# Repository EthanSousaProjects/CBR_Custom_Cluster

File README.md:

# CBR_Custom_Cluster

A custom cluster design for my CBR 125RW6 (2006 carburetor model) to replace the old large mechanical cluster with a smaller simpler design.

The `references` folder contains details on set things on the bike (eg. hole position dimensions, resistance of stock sensor) and thus design requirements, calculations and decisions can be found here.

## License

There are three licenses for this project. All code falls under the AGPLV3 license, all hardware designs fall under the CERN-OHL-S license, all artwork and documentation in the READMEs related to this project are under the CC By-SA license.

This project is based around creating a dash for a honda motorcycle. I have no affiliation with honda or its subsidiaries. This is not an official honda project in anyway.

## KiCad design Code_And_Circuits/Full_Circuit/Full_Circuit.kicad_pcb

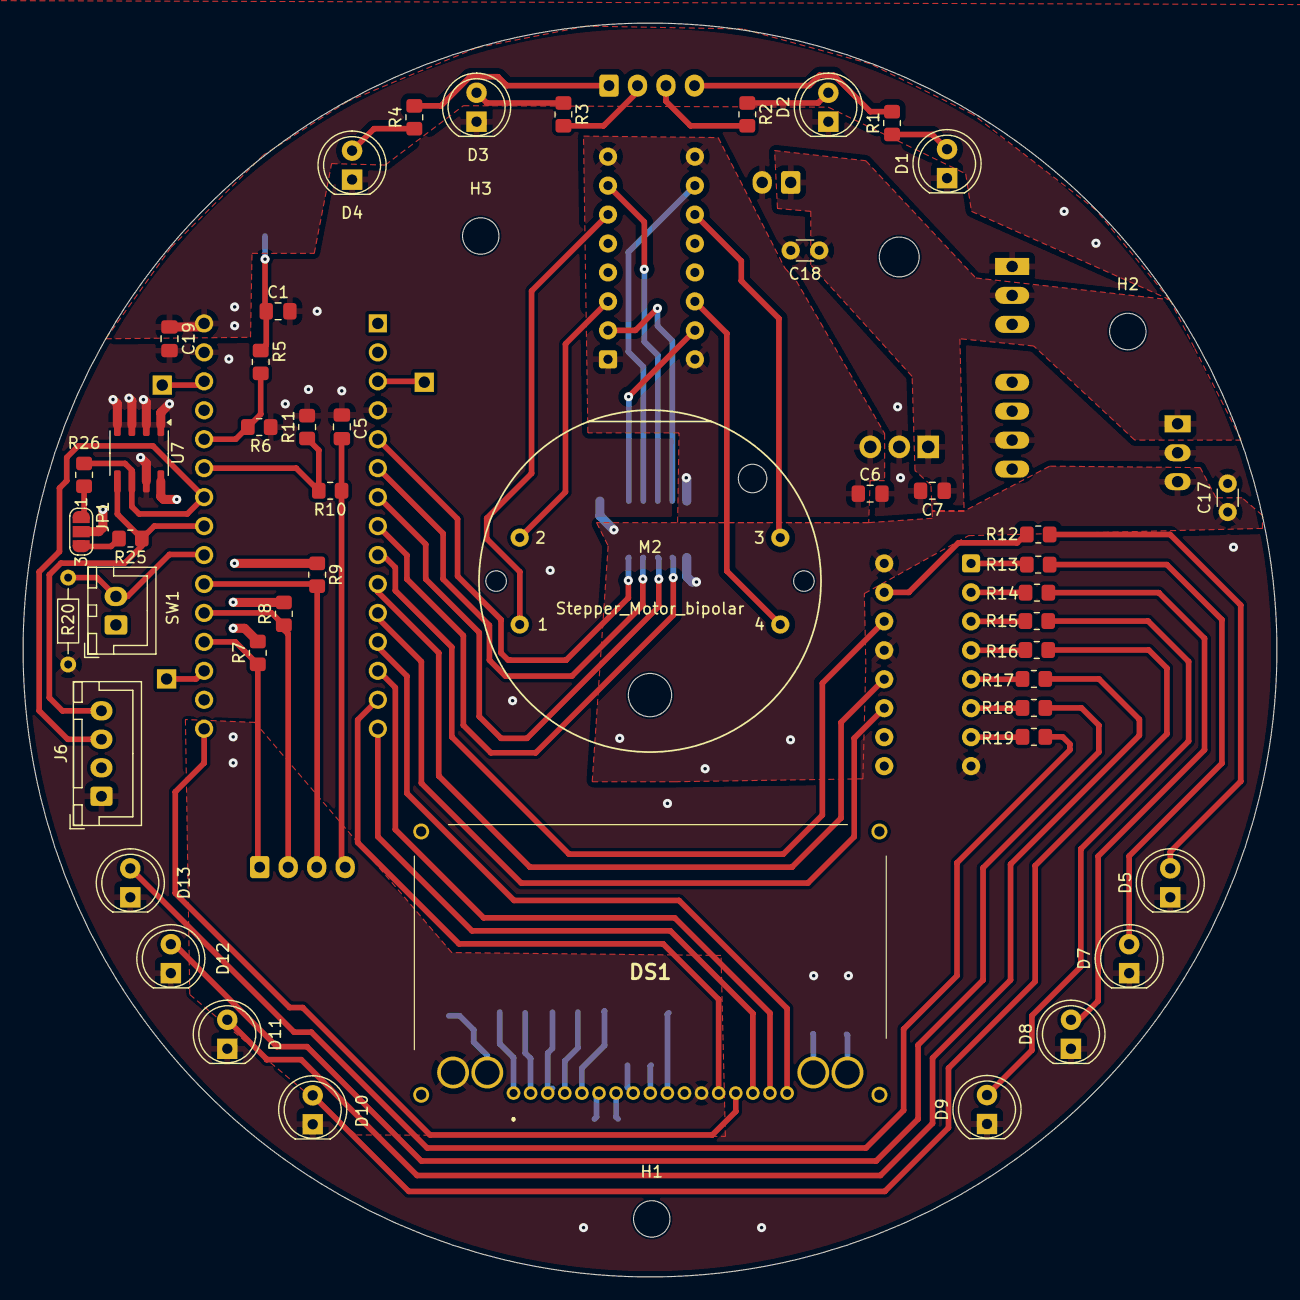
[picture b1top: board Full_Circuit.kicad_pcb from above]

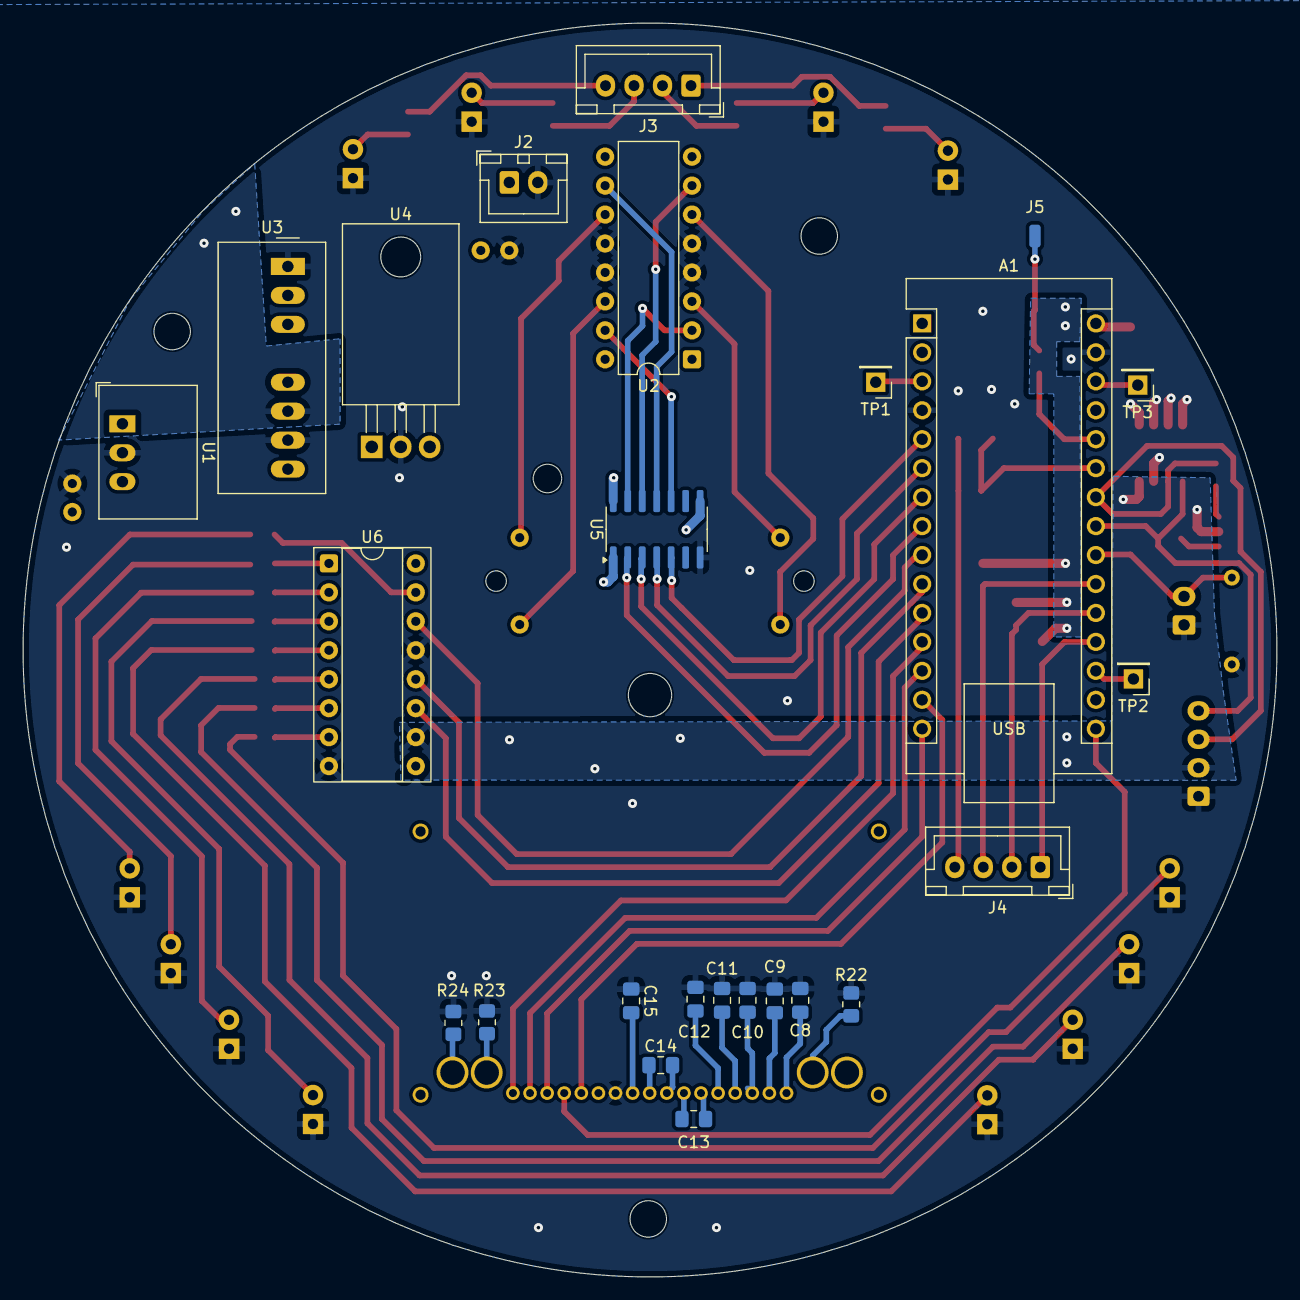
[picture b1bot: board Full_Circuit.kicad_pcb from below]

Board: 2 copper layers, 110.0 x 110.0 mm, 76 parts (25 on the bottom side), 77 nets.

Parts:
A1: Arduino_Nano_ESP32; Arduino_Nano
C1, C5: 1000PF; C_0805_2012Metric_Pad1.18x1.45mm_HandSolder
C6, C19: 0.1 uF; C_0805_2012Metric_Pad1.18x1.45mm_HandSolder
C7: 0.33uF; C_0805_2012Metric_Pad1.18x1.45mm_HandSolder
C8, C9, C10, C11, C12, C13, C14, C15: 1uF; C_0805_2012Metric_Pad1.18x1.45mm_HandSolder
C17, C18: 10 uF; C_Disc_D3.0mm_W1.6mm_P2.50mm
D1: LED_Right_Indicator(Yellow_LTH5MM12VFR4700); LED_D5.0mm
D2: LED_High_Beam(Blue_LTH5MM12VFR4600); LED_D5.0mm
D3: LED_Neutral(Green_LTH5MM12VFR4500); LED_D5.0mm
D4: LED_Left_Indicator(Yellow_LTH5MM12VFR4700); LED_D5.0mm
D5, D7, D8, D9, D10, D11, D12, D13: LED_2.2V_20ma; LED_D5.0mm
DS1: NHD-C12832A1Z-FS_RGB_-FBW-3V; NHDC12832A1ZFSRGBFBW3V
H1, H2, H3: MountingHole; MountingHole_3.2mm_M3
J2: Main_Power_In_JST-XH; JST_XH_B2B-XH-A_1x02_P2.50mm_Vertical
J3: Warning_Lights_JST-XH; JST_XH_B4B-XH-A_1x04_P2.50mm_Vertical
J4: Signals_RPM_Temp_Fuel_JST-XH; JST_XH_B4B-XH-A_1x04_P2.50mm_Vertical
J5: Speed_Pulser_Setup_Signal_JST-XH; SolderWirePad_1x01_SMD_1x2mm
J6: Alphanumeric_Qwiick_JST-XH; JST_XH_B4B-XH-A_1x04_P2.50mm_Vertical
JP1: Pull up Jumper; SolderJumper-3_P1.3mm_Open_RoundedPad1.0x1.5mm_NumberLabels
M2: Stepper_Motor_bipolar; X27-168
N1: Tachometer Reference; Dial_Gauge_Reference_CBF600
R1, R2, R3, R4: 200R; R_0805_2012Metric_Pad1.20x1.40mm_HandSolder
R5, R10: 3.3KR; R_0805_2012Metric_Pad1.20x1.40mm_HandSolder
R6, R7, R8, R11: 1KR; R_0805_2012Metric_Pad1.20x1.40mm_HandSolder
R9: 510R; R_0805_2012Metric_Pad1.20x1.40mm_HandSolder
R12, R13, R14, R15, R16, R17, R18, R19: 100R; R_0805_2012Metric_Pad1.20x1.40mm_HandSolder
R20: 10KR; R_Axial_DIN0204_L3.6mm_D1.6mm_P7.62mm_Horizontal
R22: 56R; R_0805_2012Metric_Pad1.20x1.40mm_HandSolder
R23, R24: 6.8R; R_0805_2012Metric_Pad1.20x1.40mm_HandSolder
R25, R26: 4.7KR; R_0805_2012Metric_Pad1.20x1.40mm_HandSolder
SW1: SW_Push_JST-XH_Input; JST_XH_B2B-XH-A_1x02_P2.50mm_Vertical
TP1, TP2, TP3: TestPoint; PinHeader_1x01_P2.54mm_Vertical
U1: R-78E3.3-0.5; Converter_DCDC_RECOM_R-78E-0.5_THT
U2: L293D; DIP-16_W7.62mm
U3: TEC2-1219WI; Converter_DCDC_TRACO_TMR-xxxx_THT
U4: L7805; TO-220-3_Horizontal_TabDown
U5: TXB0104D; SOIC-14_3.9x8.7mm_P1.27mm
U6: 74HC595; DIP-16_W7.62mm_Socket
U7: CAT24C128; SOIC-8_3.9x4.9mm_P1.27mm

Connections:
+3.3V: C17.1, DS1.12 (VDD), DS1.A1 (COMMON_ANODE), J6.2, JP1.2 (C), SW1.1, U1.3 (OUT), U5.1 (VCCA), U5.8 (OE), U6.10 (~SRCLR), U6.16 (VCC), U7.8 (VCC)
+5V: C6.1, U2.1 (EN1,2), U2.8 (VCC2), U2.9 (EN3,4), U2.16 (VCC1), U4.3 (OUT), U5.14 (VCCB)
+9V: A1.30 (VIN), C19.1, R7.2, R8.2, R9.1, U3.6 (+Vout)
+12V: C7.1, C18.1, J2.1, U1.1 (IN), U3.2 (+Vin), U4.1 (IN)
/Data_Display_Controller/A0: A1.15 (D12/CIPO), DS1.15 (A0)
/Data_Display_Controller/Bar_RCLK: A1.10 (D7), U6.12 (RCLK)
/Data_Display_Controller/Bar_SER: A1.9 (D6), U6.14 (SER)
/Data_Display_Controller/Bar_SRCLK: A1.11 (D8), U6.11 (SRCLK)
/Data_Display_Controller/Button_A: A1.22 (A3), R20.2, SW1.2
/Data_Display_Controller/COPI(MOSI): A1.14 (D11/COPI), DS1.13 (SI)
/Data_Display_Controller/Coolant: A1.21 (A2), J4.3, R9.2
/Data_Display_Controller/Fuel_A: A1.19 (A0), J4.1, R7.1
/Data_Display_Controller/Fuel_B: A1.20 (A1), J4.2, R8.1
/Data_Display_Controller/I2C SCL: A1.24 (SCL/A5), J6.3, R26.1, U7.6 (SCL)
/Data_Display_Controller/I2C SDA: A1.23 (SDA/A4), J6.4, R25.1, U7.5 (SDA)
/Data_Display_Controller/RES(RST): A1.13 (D10/CS), DS1.16 (~RES)
/Data_Display_Controller/RPM_Pulse: A1.25 (A6), R10.2, R11.1
/Data_Display_Controller/SPI_CS(CS1B): A1.12 (D9), DS1.17 (CS1B)
/Data_Display_Controller/SPI_SCK: A1.16 (D13/SCK), DS1.14 (SCL)
/Data_Display_Controller/Speed_Pulse: A1.26 (A7), R5.2, R6.1
/Data_Display_Controller/Tach_A1: A1.8 (D5), U5.2 (A1)
/Data_Display_Controller/Tach_A2: A1.7 (D4), U5.3 (A2)
/Data_Display_Controller/Tach_A3: A1.6 (D3), U5.4 (A3)
/Data_Display_Controller/Tach_A4: A1.5 (D2), U5.5 (A4)
GND: A1.4 (GND), A1.29 (GND), C1.2, C5.1, C6.2, C7.2, C8.1, C9.1, C10.1, C11.1, C12.1, C15.1, C17.2, C18.2, C19.2, D1.1 (K), D2.1 (K), D3.1 (K), D4.1 (K), D5.1 (K), D7.1 (K), D8.1 (K), D9.1 (K), D10.1 (K), D11.1 (K), D12.1 (K), D13.1 (K), DS1.11 (VSS), J2.2, J6.1, R6.2, R11.2, R20.1, R22.2, R23.2, R24.2, U1.2 (GND), U2.4 (GND), U2.5 (GND), U2.12 (GND), U2.13 (GND), U3.1 (-Vin), U3.7 (-Vout), U4.2 (GND), U5.7 (GND), U6.8 (GND), U6.13 (~OE), U7.1 (A0), U7.2 (A1), U7.3 (A2), U7.4 (GND), U7.7 (WP)
unnamed: A1.18 (B0), TP2.1
unnamed: A1.28 (B1), TP3.1
unnamed: A1.3 (~RESET), TP1.1
unnamed: D1.2 (A), R1.1
unnamed: D2.2 (A), R2.1
unnamed: D3.2 (A), R3.1
unnamed: D4.2 (A), R4.1
unnamed: D5.2 (A), R12.1
unnamed: D7.2 (A), R13.1
unnamed: D8.2 (A), R14.1
unnamed: D9.2 (A), R15.1
unnamed: D10.2 (A), R16.1
unnamed: D11.2 (A), R17.1
unnamed: D12.2 (A), R18.1
unnamed: D13.2 (A), R19.1
unnamed: C14.2, DS1.8 (C1+)
unnamed: C14.1, DS1.9 (C1-)
unnamed: C13.1, DS1.7 (C2+)
unnamed: C13.2, DS1.6 (C2-)
unnamed: DS1.K2 (CATHODE_1), R23.1
unnamed: DS1.K3 (CATHODE_2), R24.1
unnamed: DS1.K1 (CATHODE_), R22.1
unnamed: C8.2, DS1.1 (V0)
unnamed: C9.2, DS1.2 (V1)
unnamed: C10.2, DS1.3 (V2)
unnamed: C11.2, DS1.4 (V3)
unnamed: C12.2, DS1.5 (V4)
unnamed: C15.2, DS1.10 (VOUT)
unnamed: J3.1, R4.2
unnamed: J3.2, R3.2
unnamed: J3.3, R2.2
unnamed: J3.4, R1.2
unnamed: C5.2, J4.4, R10.1
unnamed: C1.1, J5.1, R5.1
unnamed: JP1.1 (A), R26.2
unnamed: JP1.3 (B), R25.2
unnamed: M2.2 (-), U2.3 (1Y)
unnamed: U2.2 (1A), U5.13 (B1)
unnamed: U2.7 (2A), U5.12 (B2)
unnamed: M2.1, U2.6 (2Y)
unnamed: U2.10 (3A), U5.11 (B3)
unnamed: M2.3, U2.11 (3Y)
unnamed: U2.15 (4A), U5.10 (B4)
unnamed: M2.4, U2.14 (4Y)
unnamed: R12.2, U6.15 (QA)
unnamed: R13.2, U6.1 (QB)
unnamed: R14.2, U6.2 (QC)
unnamed: R15.2, U6.3 (QD)
unnamed: R16.2, U6.4 (QE)
unnamed: R17.2, U6.5 (QF)
unnamed: R18.2, U6.6 (QG)
unnamed: R19.2, U6.7 (QH)

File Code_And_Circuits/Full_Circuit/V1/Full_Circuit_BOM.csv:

"Reference","Qty","Value","DNP","Exclude from BOM","Exclude from Board","Footprint","Datasheet"
"A1","1","Arduino_Nano_ESP32","","","","Module:Arduino_Nano","https://docs.arduino.cc/resources/datasheets/ABX00083-datasheet.pdf"
"A3","1","Arduino_Nano_ESP32","DNP","","Excluded from board","Module:Arduino_Nano","https://docs.arduino.cc/resources/datasheets/ABX00083-datasheet.pdf"
"C1,C5","2","1000PF","","","","Capacitor_SMD:C_0805_2012Metric_Pad1.18x1.45mm_HandSolder","~"
"C2,C3,C4","3","1000PF","DNP","","Excluded from board","Capacitor_THT:C_Disc_D3.0mm_W2.0mm_P2.50mm","~"
"C6,C19","2","0.1 uF","","","","Capacitor_SMD:C_0805_2012Metric_Pad1.18x1.45mm_HandSolder","~"
"C7","1","0.33uF","","","","Capacitor_SMD:C_0805_2012Metric_Pad1.18x1.45mm_HandSolder","~"
"C8,C9,C10,C11,C12,C13,C14,C15","8","1uF","","","","Capacitor_SMD:C_0805_2012Metric_Pad1.18x1.45mm_HandSolder","~"
"C16","1","100uF","DNP","","Excluded from board","Capacitor_SMD:C_0805_2012Metric_Pad1.18x1.45mm_HandSolder","~"
"C17,C18","2","10 uF","","","","Capacitor_THT:C_Disc_D3.0mm_W1.6mm_P2.50mm","~"
"D1","1","LED_Right_Indicator(Yellow_LTH5MM12VFR4700)","","","","LED_THT:LED_D5.0mm","~"
"D2","1","LED_High_Beam(Blue_LTH5MM12VFR4600)","","","","LED_THT:LED_D5.0mm","~"
"D3","1","LED_Neutral(Green_LTH5MM12VFR4500)","","","","LED_THT:LED_D5.0mm","~"
"D4","1","LED_Left_Indicator(Yellow_LTH5MM12VFR4700)","","","","LED_THT:LED_D5.0mm","~"
"D5,D7,D8,D9,D10,D11,D12,D13","8","LED_2.2V_20ma","","","","LED_THT:LED_D5.0mm","~"
"D6,D14","2","1N4007","DNP","","Excluded from board","Diode_THT:D_DO-41_SOD81_P10.16mm_Horizontal","http://www.vishay.com/docs/88503/1n4001.pdf"
"DS1","1","NHD-C12832A1Z-FS_RGB_-FBW-3V","","","","Added_Footprints:NHDC12832A1ZFSRGBFBW3V",""
"H1,H2,H3","3","MountingHole","","Excluded from BOM","","MountingHole:MountingHole_3.2mm_M3","~"
"H4","1","MountingHole","DNP","Excluded from BOM","Excluded from board","MountingHole:MountingHole_3.2mm_M3","~"
"J1","1","Micro_SD_Card_Slot","DNP","","Excluded from board","Connector_Card:microSD_HC_Wuerth_693072010801","https://www.we-online.com/components/products/datasheet/6930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"
"J2","1","Main_Power_In_JST-XH","","","","Connector_JST:JST_XH_B2B-XH-A_1x02_P2.50mm_Vertical","~"
"J3","1","Warning_Lights_JST-XH","","","","Connector_JST:JST_XH_B4B-XH-A_1x04_P2.50mm_Vertical","~"
"J4","1","Signals_RPM_Temp_Fuel_JST-XH","","","","Connector_JST:JST_XH_B4B-XH-A_1x04_P2.50mm_Vertical","~"
"J5","1","Speed_Pulser_Setup_Signal_JST-XH","","","","Connector_Wire:SolderWirePad_1x01_SMD_1x2mm","~"
"J6","1","Alphanumeric_Qwiick_JST-XH","","","","Connector_JST:JST_XH_B4B-XH-A_1x04_P2.50mm_Vertical","~"
"JP1","1","Pull up Jumper","","Excluded from BOM","","Jumper:SolderJumper-3_P1.3mm_Open_RoundedPad1.0x1.5mm_NumberLabels","~"
"JP2","1","address jumper A2","DNP","Excluded from BOM","Excluded from board","Jumper:SolderJumper-3_P1.3mm_Bridged12_RoundedPad1.0x1.5mm_NumberLabels","~"
"JP3","1","address jumper A1","DNP","Excluded from BOM","Excluded from board","Jumper:SolderJumper-3_P1.3mm_Bridged12_RoundedPad1.0x1.5mm_NumberLabels","~"
"JP4","1","address jumper A0","DNP","Excluded from BOM","Excluded from board","Jumper:SolderJumper-3_P1.3mm_Bridged12_RoundedPad1.0x1.5mm_NumberLabels","~"
"JP5","1","Write Protection Jumper","DNP","Excluded from BOM","Excluded from board","Jumper:SolderJumper-2_P1.3mm_Open_RoundedPad1.0x1.5mm","~"
"M1","1","GY-GPS6MV2","DNP","","Excluded from board","Added_Footprints:GY-GPS6MV2",""
"M2","1","Stepper_Motor_bipolar","","","","Added_Footprints:X27-168","http://www.infineon.com/dgdl/Application-Note-TLE8110EE_driv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"
"M3","1","Accelerometer and Gyroscope (BMI160 Module)","DNP","","Excluded from board","Added_Footprints:BMI160_Module",""
"N1","1","Tachometer Reference","","","","Added_Footprints:Dial_Gauge_Reference_CBF600","~"
"R1,R2,R3,R4","4","200R","","","","Resistor_SMD:R_0805_2012Metric_Pad1.20x1.40mm_HandSolder","~"
"R5,R10","2","3.3KR","","","","Resistor_SMD:R_0805_2012Metric_Pad1.20x1.40mm_HandSolder","~"
"R6,R7,R8,R11","4","1KR","","","","Resistor_SMD:R_0805_2012Metric_Pad1.20x1.40mm_HandSolder","~"
"R9","1","510R","","","","Resistor_SMD:R_0805_2012Metric_Pad1.20x1.40mm_HandSolder","~"
"R12,R13,R14,R15,R16,R17,R18,R19","8","100R","","","","Resistor_SMD:R_0805_2012Metric_Pad1.20x1.40mm_HandSolder","~"
"R20","1","10KR","","","","Resistor_THT:R_Axial_DIN0204_L3.6mm_D1.6mm_P7.62mm_Horizontal","~"
"R22","1","56R","","","","Resistor_SMD:R_0805_2012Metric_Pad1.20x1.40mm_HandSolder","~"
"R23,R24","2","6.8R","","","","Resistor_SMD:R_0805_2012Metric_Pad1.20x1.40mm_HandSolder","~"
"R25,R26","2","4.7KR","","","","Resistor_SMD:R_0805_2012Metric_Pad1.20x1.40mm_HandSolder","~"
"R27,R28,R29,R30","4","100KR","DNP","","Excluded from board","Resistor_SMD:R_0805_2012Metric_Pad1.20x1.40mm_HandSolder","~"
"SW1","1","SW_Push_JST-XH_Input","","","","Connector_JST:JST_XH_B2B-XH-A_1x02_P2.50mm_Vertical","~"
"TP1,TP2,TP3","3","TestPoint","","","","Connector_PinHeader_2.54mm:PinHeader_1x01_P2.54mm_Vertical","~"
"TP4,TP5,TP6","3","TestPoint","DNP","","Excluded from board","Connector_PinHeader_1.00mm:PinHeader_1x01_P1.00mm_Vertical","~"
"U1","1","R-78E3.3-0.5","","","","Converter_DCDC:Converter_DCDC_RECOM_R-78E-0.5_THT","https://www.recom-power.com/pdf/Innoline/R-78Exx-0.5.pdf"
"U2","1","L293D","","","","Package_DIP:DIP-16_W7.62mm","http://www.ti.com/lit/ds/symlink/l293.pdf"
"U3","1","TEC2-1219WI","","","","Converter_DCDC:Converter_DCDC_TRACO_TMR-xxxx_THT","https://www.tracopower.com/products/tec2wi.pdf"
"U4","1","L7805","","","","Package_TO_SOT_THT:TO-220-3_Horizontal_TabDown","http://www.st.com/content/ccc/resource/technical/document/da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"
"U5","1","TXB0104D","","","","Package_SO:SOIC-14_3.9x8.7mm_P1.27mm","http://www.ti.com/lit/ds/symlink/txb0104.pdf"
"U6","1","74HC595","","","","Package_DIP:DIP-16_W7.62mm_Socket","http://www.ti.com/lit/ds/symlink/sn74hc595.pdf"
"U7","1","CAT24C128","","","","Package_SO:SOIC-8_3.9x4.9mm_P1.27mm","https://www.onsemi.com/pub/Collateral/CAT24C128-D.PDF"

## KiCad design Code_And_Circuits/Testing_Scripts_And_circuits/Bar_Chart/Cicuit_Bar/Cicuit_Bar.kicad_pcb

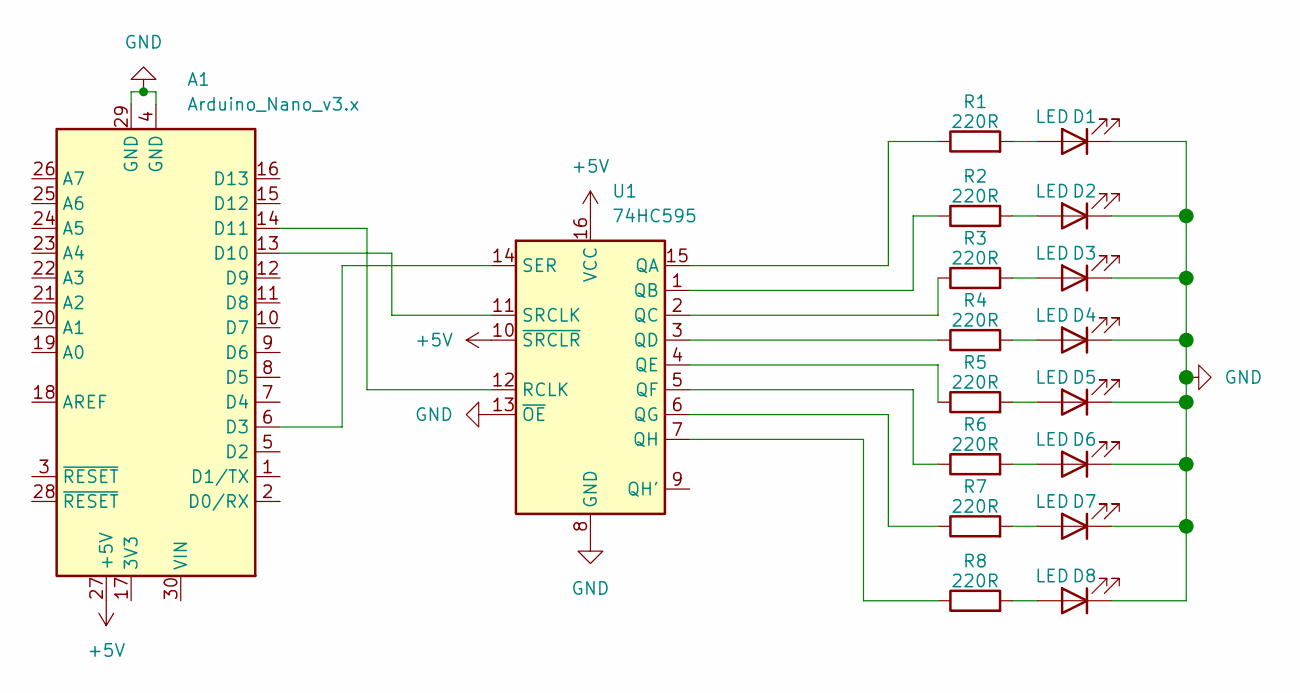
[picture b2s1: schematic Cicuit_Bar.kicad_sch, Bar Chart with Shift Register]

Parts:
A1: Arduino_Nano_v3.x; Arduino_Nano
D1, D2, D3, D4, D5, D6, D7, D8: LED; LED_D5.0mm
R1, R2, R3, R4, R5, R6, R7, R8: 220R; R_Axial_DIN0204_L3.6mm_D1.6mm_P7.62mm_Horizontal
U1: 74HC595; DIP-16_W7.62mm_Socket

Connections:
+5V: A1.27 (+5V), U1.10 (~SRCLR), U1.16 (VCC)
GND: A1.4 (GND), A1.29 (GND), D1.1 (K), D2.1 (K), D3.1 (K), D4.1 (K), D5.1 (K), D6.1 (K), D7.1 (K), D8.1 (K), U1.8 (GND), U1.13 (~OE)
unnamed: A1.6 (D3), U1.14 (SER)
unnamed: A1.13 (D10), U1.11 (SRCLK)
unnamed: A1.14 (D11), U1.12 (RCLK)
unnamed: D1.2 (A), R1.2
unnamed: D2.2 (A), R2.2
unnamed: D3.2 (A), R3.2
unnamed: D4.2 (A), R4.2
unnamed: D5.2 (A), R5.2
unnamed: D6.2 (A), R6.2
unnamed: D7.2 (A), R7.2
unnamed: D8.2 (A), R8.2
unnamed: R1.1, U1.15 (QA)
unnamed: R2.1, U1.1 (QB)
unnamed: R3.1, U1.2 (QC)
unnamed: R4.1, U1.3 (QD)
unnamed: R5.1, U1.4 (QE)
unnamed: R6.1, U1.5 (QF)
unnamed: R7.1, U1.6 (QG)
unnamed: R8.1, U1.7 (QH)

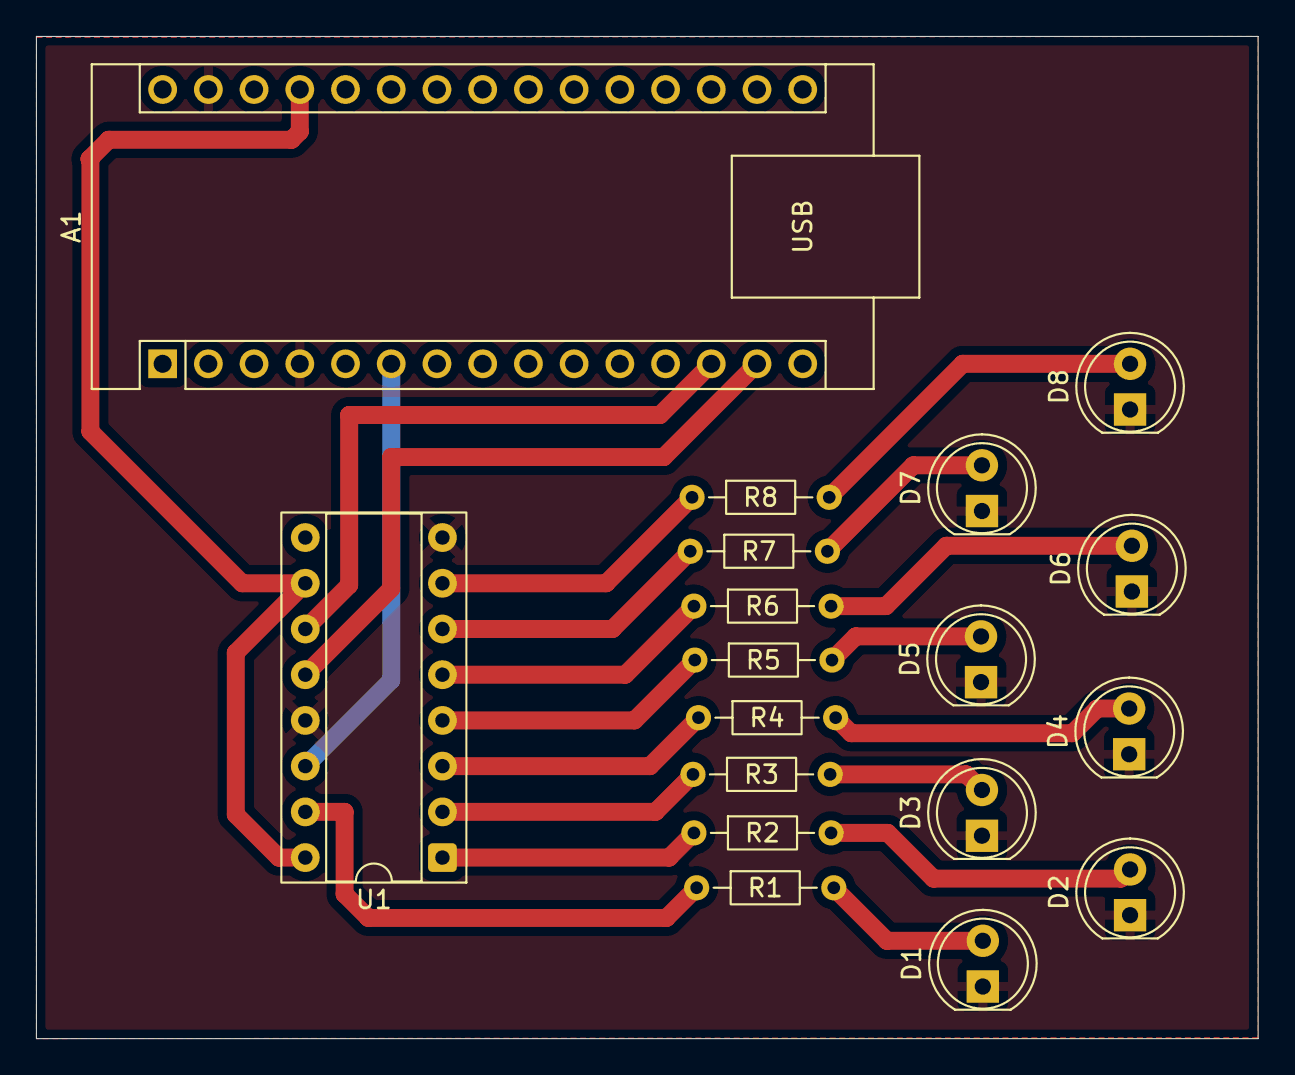
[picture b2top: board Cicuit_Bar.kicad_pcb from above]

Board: 2 copper layers, 67.9 x 55.7 mm, 18 parts (0 on the bottom side), 21 nets.

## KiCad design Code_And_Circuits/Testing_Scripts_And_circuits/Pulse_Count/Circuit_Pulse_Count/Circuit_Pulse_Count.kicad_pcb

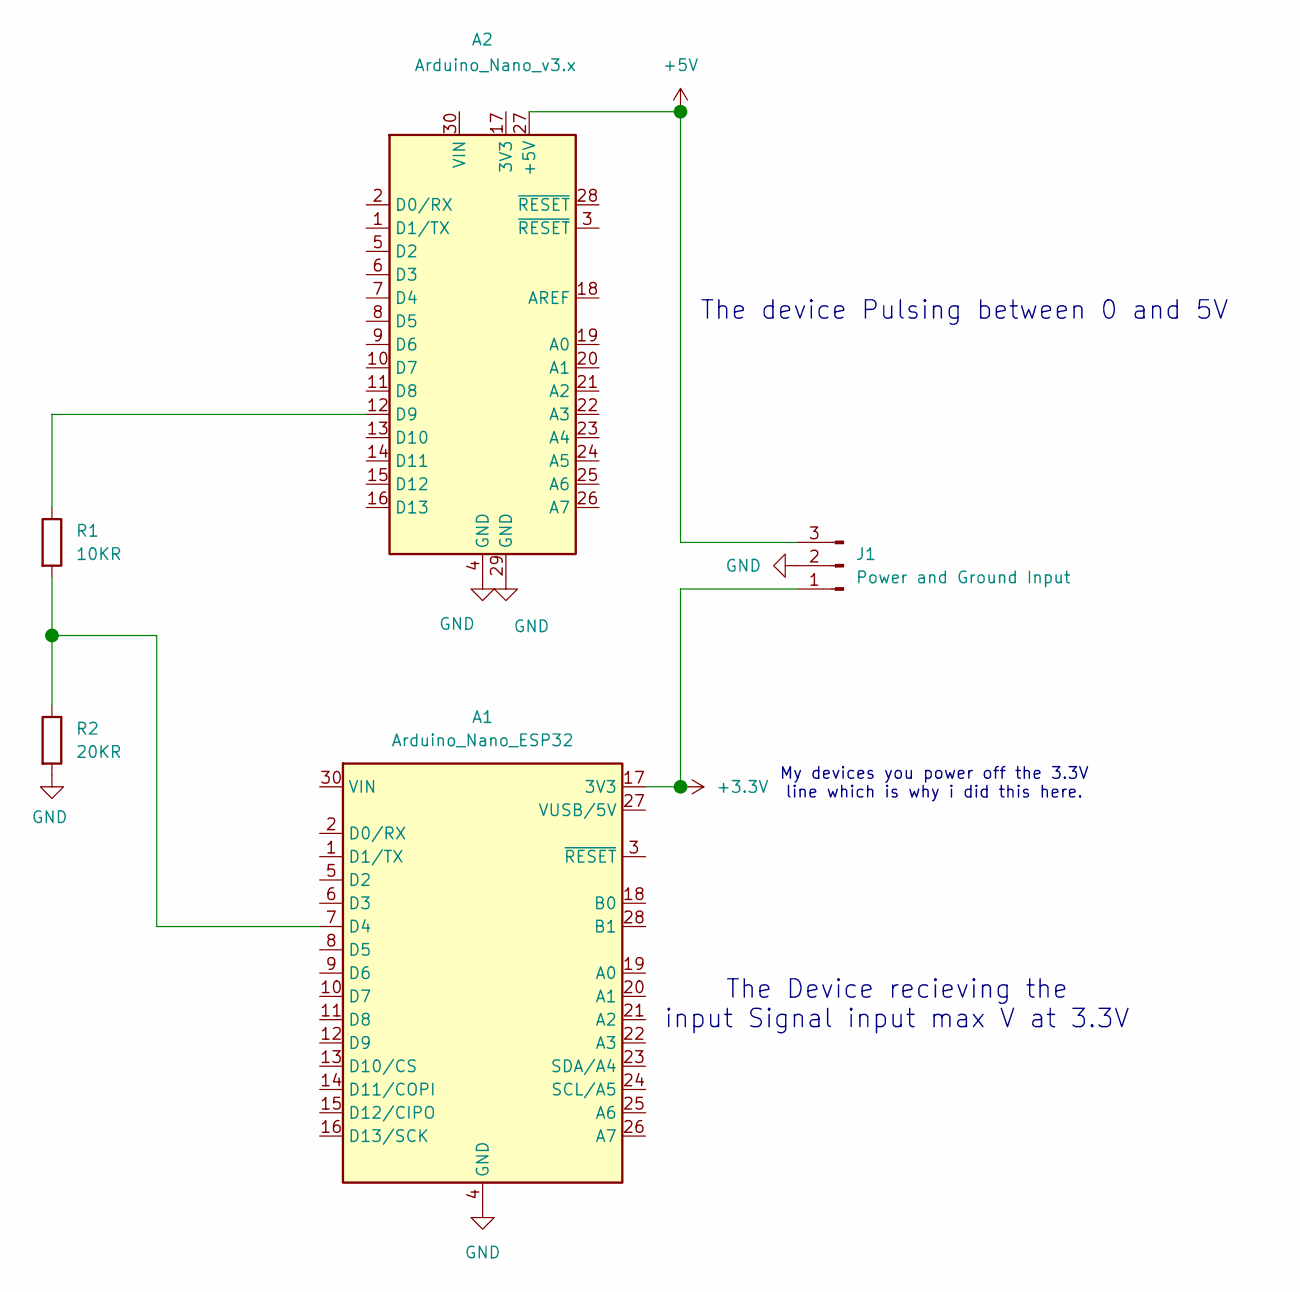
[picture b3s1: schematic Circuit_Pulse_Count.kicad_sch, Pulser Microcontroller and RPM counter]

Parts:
A1: Arduino_Nano_ESP32; Arduino_Nano
A2: Arduino_Nano_v3.x; Arduino_Nano
J1: Power and Ground Input; PinHeader_1x03_P2.54mm_Vertical
R1: 10KR; R_Axial_DIN0204_L3.6mm_D1.6mm_P7.62mm_Horizontal
R2: 20KR; R_Axial_DIN0204_L3.6mm_D1.6mm_P7.62mm_Horizontal

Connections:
+3.3V: A1.17 (3V3), J1.1
+5V: A2.27 (+5V), J1.3
GND: A1.4 (GND), A1.29 (GND), A2.4 (GND), A2.29 (GND), J1.2, R2.2
unnamed: A1.7 (D4), R1.2, R2.1
unnamed: A2.12 (D9), R1.1

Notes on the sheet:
The device Pulsing between 0 and 5V
My devices you power off the 3.3V line which is why i did this here.
The Device recieving the input Signal input max V at 3.3V

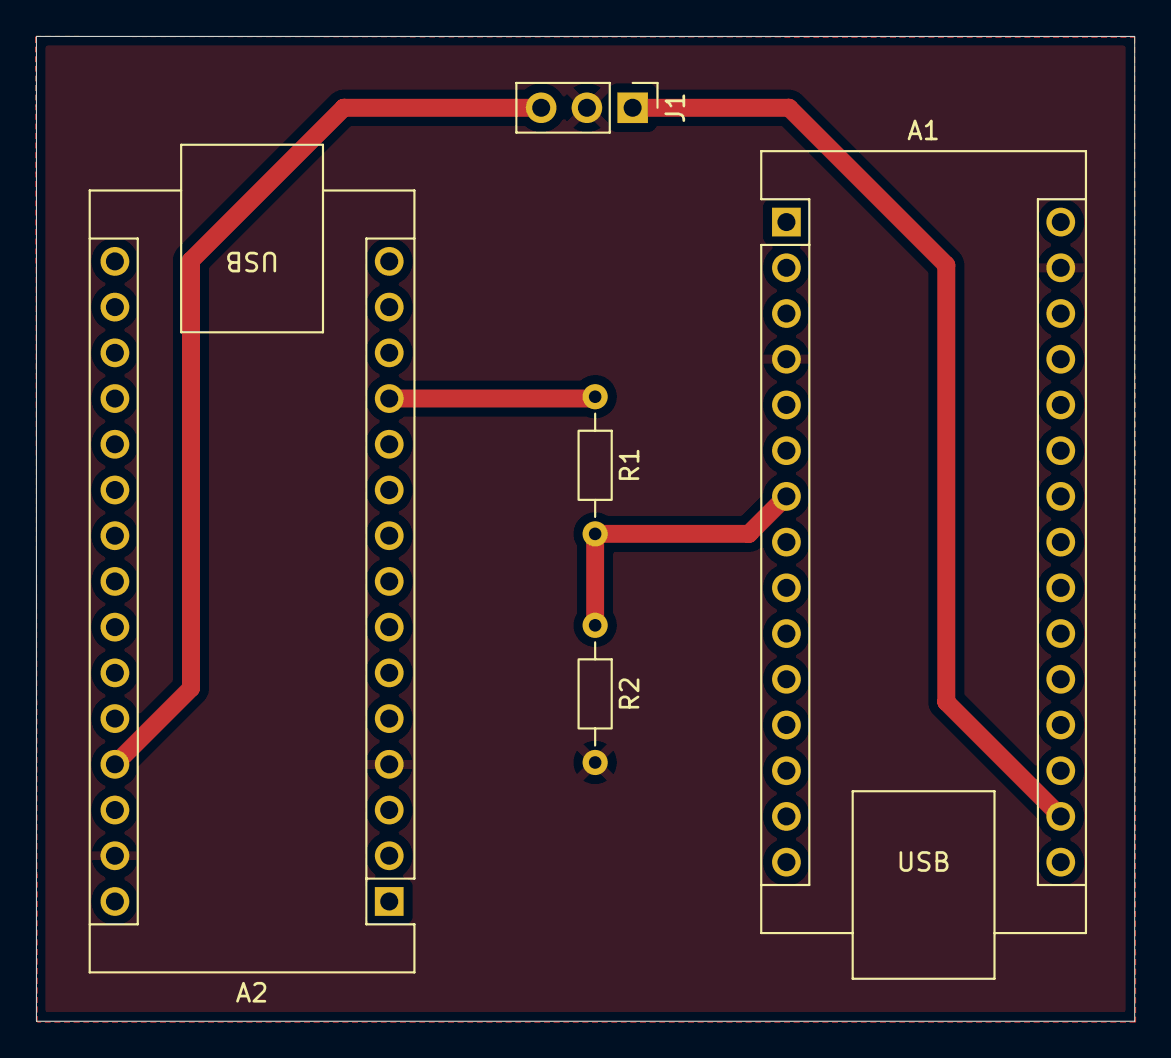
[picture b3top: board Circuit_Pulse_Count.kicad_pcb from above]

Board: 2 copper layers, 61.0 x 54.7 mm, 5 parts (0 on the bottom side), 5 nets.

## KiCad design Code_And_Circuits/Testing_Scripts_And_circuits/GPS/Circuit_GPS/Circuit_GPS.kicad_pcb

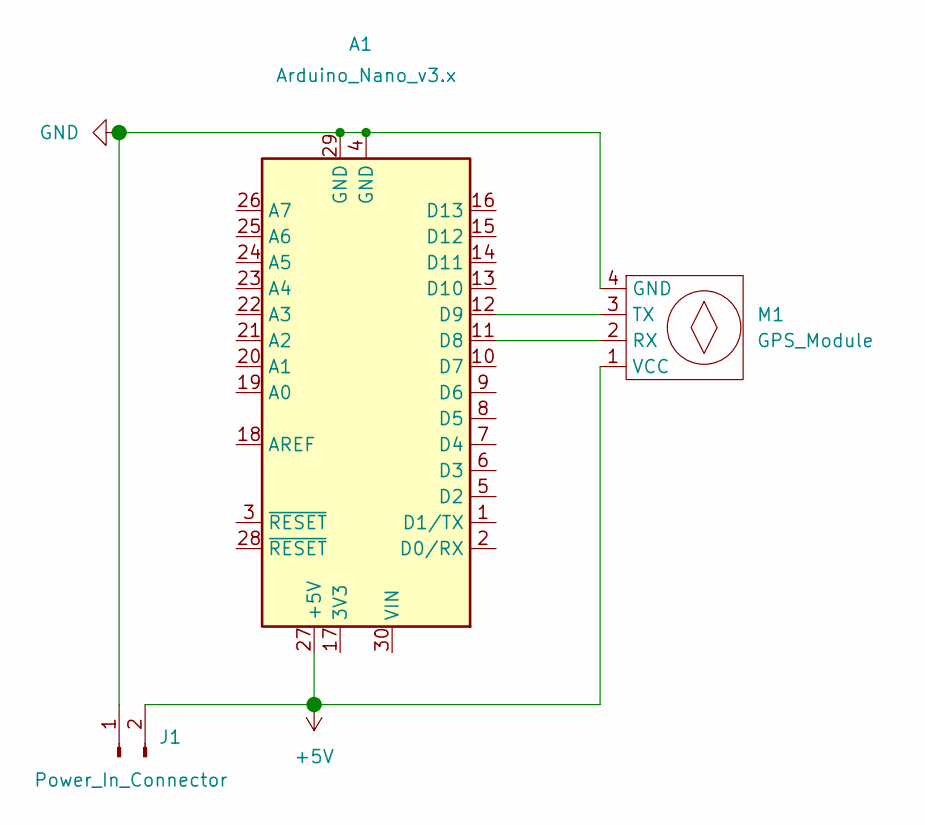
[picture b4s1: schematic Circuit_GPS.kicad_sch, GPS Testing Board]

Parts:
A1: Arduino_Nano_v3.x; Arduino_Nano
J1: Power_In_Connector; PinHeader_1x02_P2.54mm_Vertical
M1: GPS_Module; PinSocket_1x04_P2.54mm_Vertical

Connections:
+5V: A1.27 (+5V), J1.2, M1.1 (VCC)
GND: A1.4 (GND), A1.29 (GND), J1.1, M1.4 (GND)
unnamed: A1.11 (D8), M1.2 (RX)
unnamed: A1.12 (D9), M1.3 (TX)

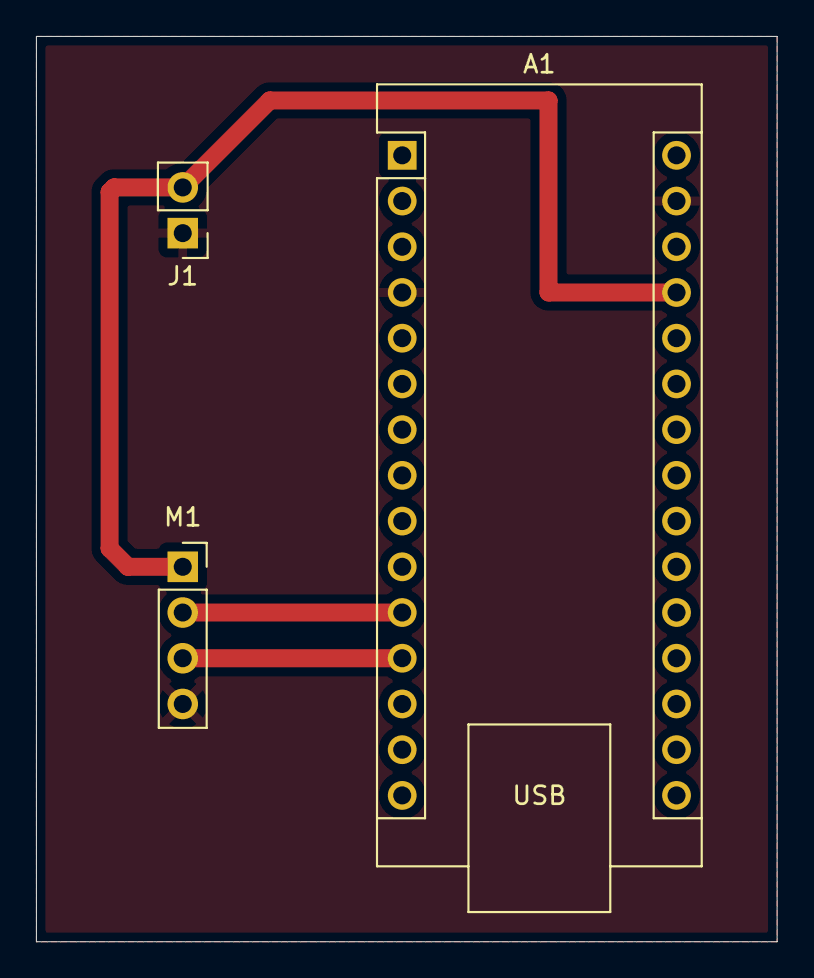
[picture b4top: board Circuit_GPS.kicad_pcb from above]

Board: 2 copper layers, 41.1 x 50.3 mm, 3 parts (0 on the bottom side), 4 nets.

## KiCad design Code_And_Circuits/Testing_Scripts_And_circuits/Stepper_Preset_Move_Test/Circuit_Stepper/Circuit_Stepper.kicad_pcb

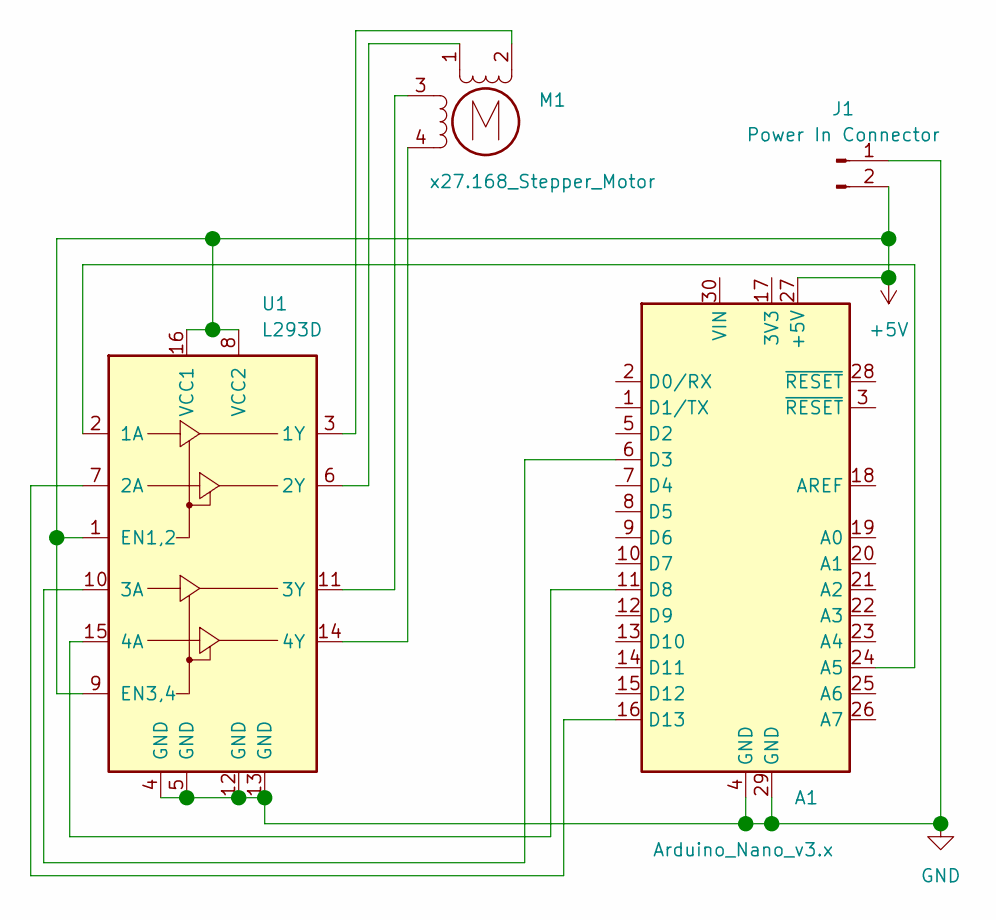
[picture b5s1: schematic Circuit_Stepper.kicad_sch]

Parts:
A1: Arduino_Nano_v3.x; Arduino_Nano
J1: Power In Connector; PinHeader_1x02_P2.54mm_Vertical
M1: x27.168_Stepper_Motor; X27-168
U1: L293D; DIP-16_W7.62mm

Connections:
+5V: A1.27 (+5V), J1.2, U1.1 (EN1,2), U1.8 (VCC2), U1.9 (EN3,4), U1.16 (VCC1)
GND: A1.4 (GND), A1.29 (GND), J1.1, U1.4 (GND), U1.5 (GND), U1.12 (GND), U1.13 (GND)
unnamed: A1.24 (A5), U1.2 (1A)
unnamed: A1.6 (D3), U1.10 (3A)
unnamed: A1.11 (D8), U1.15 (4A)
unnamed: A1.16 (D13), U1.7 (2A)
unnamed: M1.2 (-), U1.3 (1Y)
unnamed: M1.1, U1.6 (2Y)
unnamed: M1.3, U1.11 (3Y)
unnamed: M1.4, U1.14 (4Y)

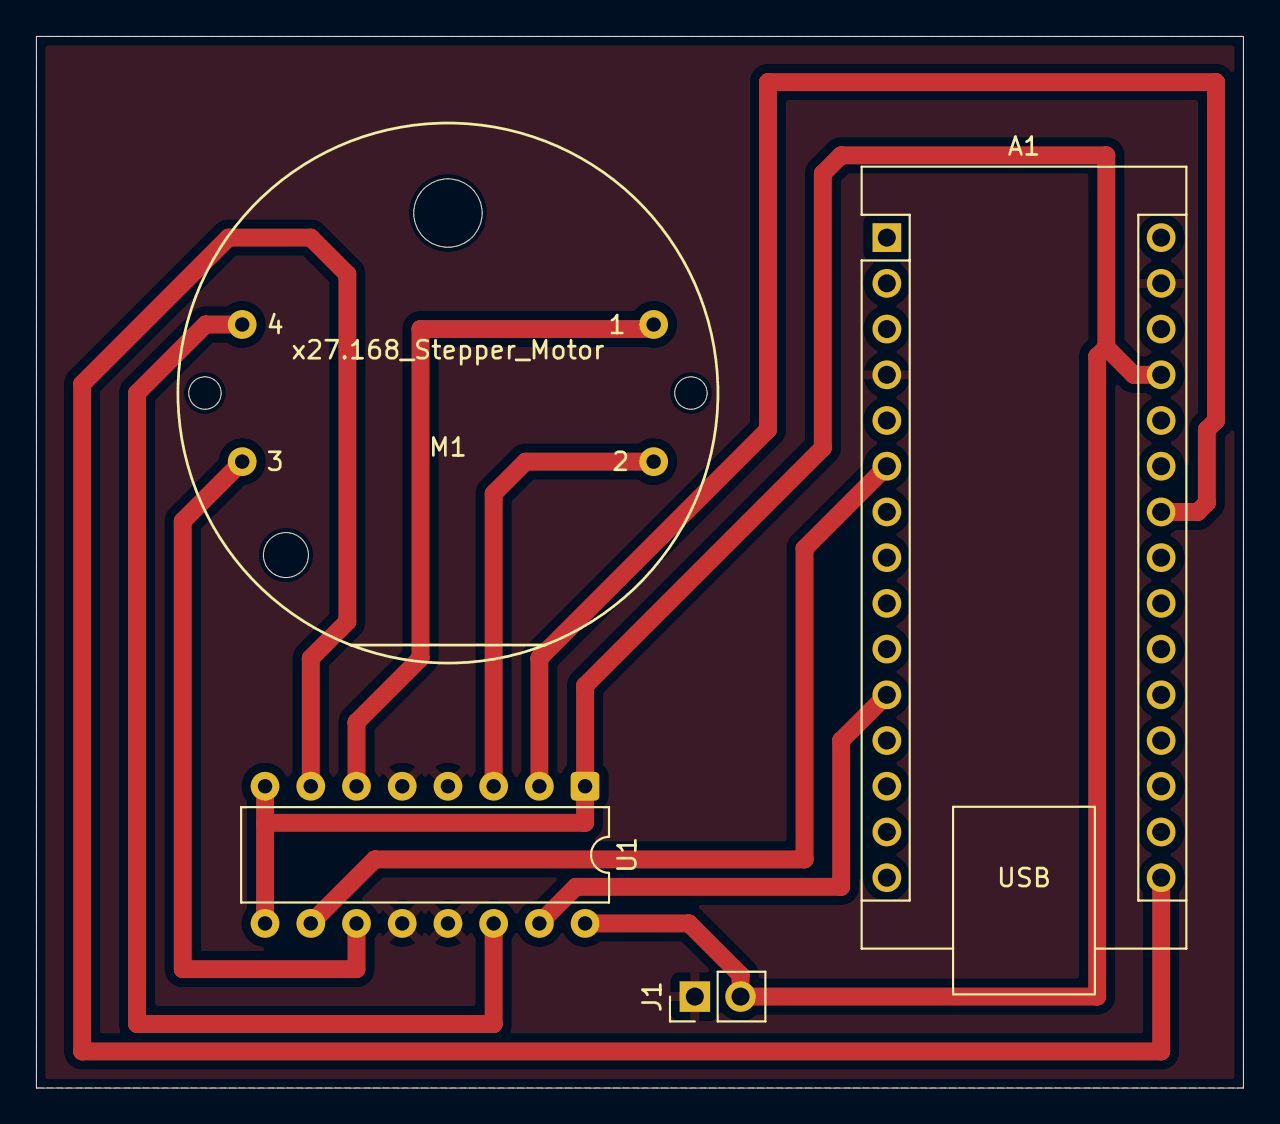
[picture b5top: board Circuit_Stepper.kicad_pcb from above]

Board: 2 copper layers, 67.1 x 58.4 mm, 4 parts (0 on the bottom side), 10 nets.

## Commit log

2025-05-29 Added in code to match the rpm signal that goes into the dash for testing purposes
2025-05-30 Added RPM changer to RPM to PWM test script through serial interface and added a User guide for the script.
2025-06-02 reorganization/ folder naming in repo for easier documentation and organization
2025-06-02 Adding in more info to RPM To PWM README.md and added in circuit scematic and PCB if you wanted to use one.
2025-06-03 Made a circuit and started the README.md for testing the movement and circuit of the 27.168 stepper motor. Code to be done.
2025-06-04 Finished the stepper testing scripts, README.md and circuit diagrams.
2025-06-04 Added a write up, circuit, testing PCB and script for adding GPS to the dash project
2025-06-11 Slight coding fix to rpm to pwm math as was error and was doing int math instead of float math
2025-06-11 Made pulse counter for rpm and speed calculations. Fine tunning required
2025-06-12 Finished code and tunning of rpm counter, adding speed calculator in please note example numbers not related to anything, adjusted README.md to better reflect on pulse counter usage and thanks to ext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
2025-06-12 Have basic cycle of numbers in alphanumeric display and circuit and PCB done. Code functionization, and HOW_TO_USE.md files to be done
2025-06-12 Finished the alphanumeric HOW_TO_USE.md file and cleaned up the code a bit.
2025-06-13 Bar chart with shift register code compleated need circuit and HOW_TO_USE.md file made
2025-06-13 Finished write up on how to use bar chart code and made circuit schematic and pcb design
2025-06-14 Fixed alphanumeric HOW_TO_USE.md error and adding a testing script, schematic and HOW_TO_USE.md for a 6 axis accelerometer and gyroscope
2025-06-16 Started to make the KiCAD scematic and PCB/s for the project slowly planning it all out
2025-06-24 Wrote up on how the fuel level sensing circuit should be designed
2025-06-25 Wrote up on the design considerations behind the coolant monitoring circuit
2025-06-26 Finished schematic need to do PCB design and get Tachometer reference
2025-06-26 Made a CAD model and technical drawing of the gauge face i want to use.
2025-06-27 Reconfired some pin assignments for cleaner layout and adding reference footprints and mostly layed out board, due to space limits logging section has been ommitted
2025-06-27 Finished PCB layout for version 1
2025-06-27 Slight modification to get more ground fill on the top layer to help with EMI
2025-06-28 Slightly adjusted layout of board and made V1 gerbers. Generated PDF schematics
2025-07-06 Reconfigered folder organisation for multiple revisions
2025-07-08 Added display test and wrote notes on the V1 PCB design
2025-11-02 Updated licence to better reflect project, software under AGPLV3 and hardware designs under CERN-OHL-S, eeprom test script also implemented
2025-12-06 Additional licence terms for graphics created in docs, TODO edit in EEprom test and customize dash test script addition
